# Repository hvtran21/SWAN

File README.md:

# Secure Wireless Authentication Network (SWAN) Electrical & Computer Engineering Class of 2025

## Overview
**SWAN (Secure Wireless Authentication Network)** is a senior capstone project focused on developing a safer, more seamless alternative to traditional RFID and NFC-based access systems.  

Current wireless access solutions, such as student ID cards or key fobs, suffer from two major issues:
1. **Security vulnerabilities** – Devices such as the Flipper Zero can easily clone, replay, or brute-force RFID/NFC signals, compromising access control systems.  
2. **Limited usability** – Cards must be presented within a few centimeters of a scanner, which is inconvenient when carrying items (e.g., food, books, bags) and detracts from user experience.

SWAN leverages **Ultra-Wideband (UWB) technology** to deliver both stronger security and automatic, hands-free authentication.  

---

## Problem Statement
Existing RFID and NFC access systems are vulnerable and inconvenient:
- **Vulnerabilities**: RFID/NFC cards transmit predictable signals that can be intercepted and cloned.  
- **User experience**: Scanning requires close proximity, forcing users to stop what they’re doing to present their ID.  

This is especially problematic in settings like dormitories or offices where secure yet convenient access is critical.

---

## Solution
SWAN provides an **automatic, secure, and user-friendly wireless authentication system** powered by **UWB**.  

Key design features:
- **Hardware**:  
  - Custom-designed PCBs  
  - **ESP32-C3 WROOM** microcontroller  
  - **Decawave DWM3000 UWB transceiver**  
- **Architecture**:  
  - A distributed network of devices with a **home anchor** that verifies access  
  - Automatic authentication within a defined UWB range (no card-swipe required)  
- **Security**:  
  - Communication encrypted using **AES-128**, the standard for low-power embedded devices  
  - Resistant to replay and cloning attacks compared to RFID/NFC
  - Back method to lost tags which includes an optical finger print reader, independent from the anchor removing depedency.
 
### What this enables
The idea is that these `tag` devices can take space in your wallet as a card, and something on your keychain.
These are items that you typically always have on your person, and want to keep import track of. In the unfortunate event 
that one of these devices are stolen, rest assured you're provided with a back biometric feature and that **two** tags 
must be present at all times.

---

## Benefits
- **Improved security**: Protects against Flipper Zero-style exploits and unauthorized duplication.  
- **Hands-free access**: Users can enter secured areas automatically, without swiping or tapping a card.  
- **Energy-efficient**: Designed with low-power embedded constraints in mind.  
- **Scalable**: Can be deployed in dorms, offices, or any facility requiring secure access.  

---

## Technology Stack
- **Embedded Hardware**: ESP32-C3 WROOM, DWM3000 UWB  
- **Firmware**: C/C++ with ESP-IDF and Arduino frameworks  
- **Networking**: UWB communication protocol, AES-128 encryption  
- **Custom PCBs**: Designed for modularity and integration with door access hardware

---

# Pictures

## Tag PCB v3

## Home Anchor PCB v1

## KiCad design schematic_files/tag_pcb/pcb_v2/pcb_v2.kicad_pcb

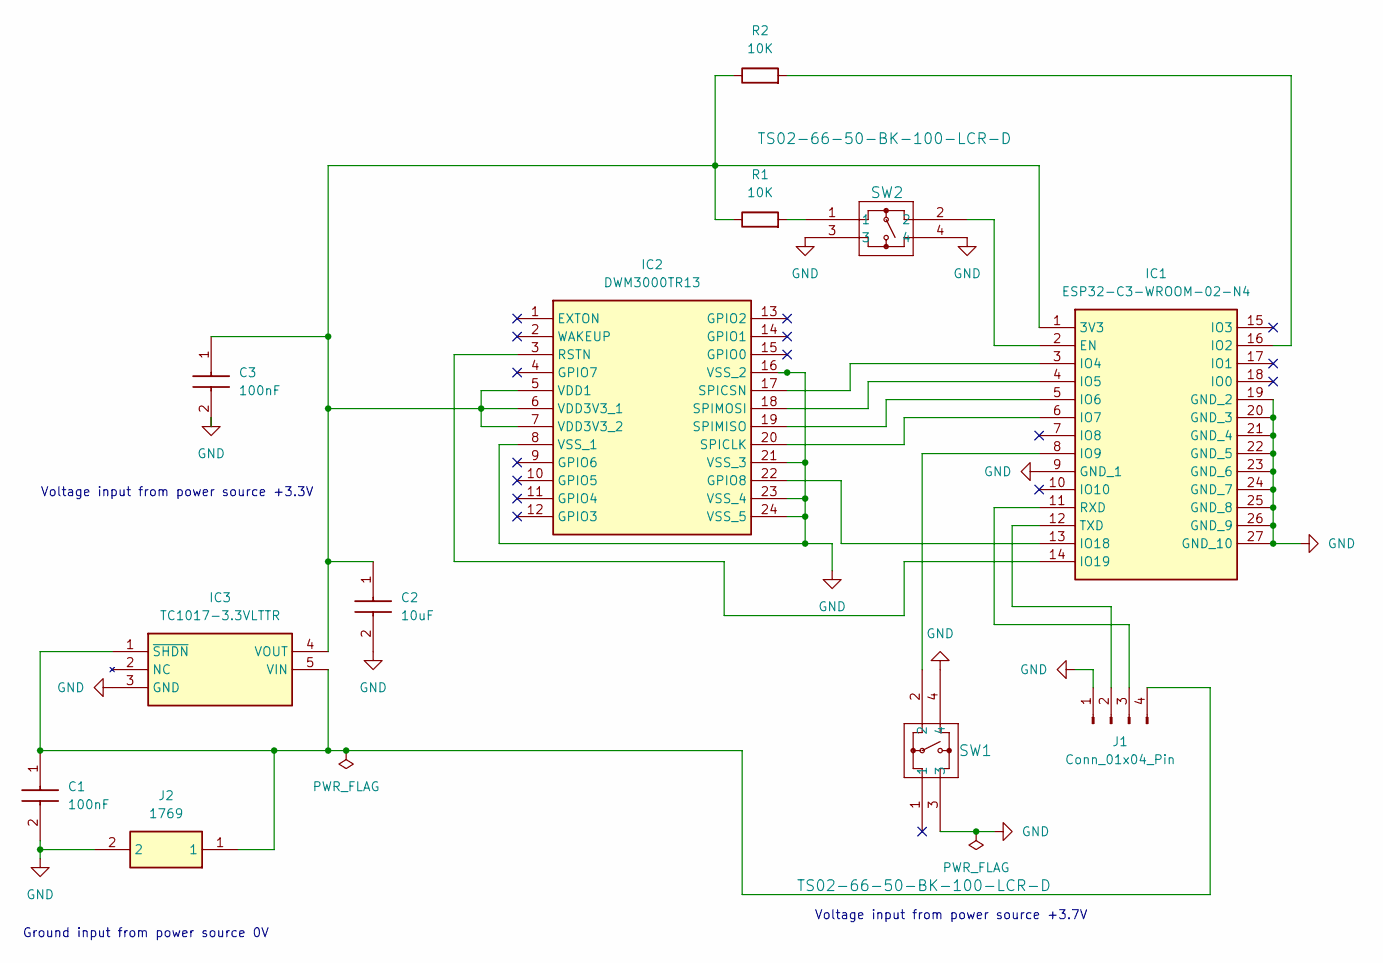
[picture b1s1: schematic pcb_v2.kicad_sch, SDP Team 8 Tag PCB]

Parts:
C1, C3: 100nF; CAPC2012X94N; Mouser Part Number 581-KAM21BR71H104JT
C2: 10uF; CAPC2012X140N; Mouser Part Number 81-GCM21BD70J106KE2L
IC1: ESP32-C3-WROOM-02-N4; ESP32C3WROOM02N4; Mouser Part Number 356-ESP32C3WROOM02N4
IC2: DWM3000TR13; XCVR_DWM3000TR13; Mouser Part Number 772-DWM3000TR13
IC3: TC1017-3.3VLTTR; SOT65P210X110-5N; Mouser Part Number 579-TC1017-3.3VLTTR
J1: Conn_01x04_Pin; PinHeader_1x04_P2.54mm_Vertical
J2: 1769; Mouser Part Number 485-1769
R1, R2: 10K; RESC3216X65N
SW1, SW2: TS02-66-50-BK-100-LCR-D; 6mm_push_button_footprint

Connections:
GND: C1.2, C2.2, C3.2, IC1.9 (GND_1), IC1.19 (GND_2), IC1.20 (GND_3), IC1.21 (GND_4), IC1.22 (GND_5), IC1.23 (GND_6), IC1.24 (GND_7), IC1.25 (GND_8), IC1.26 (GND_9), IC1.27 (GND_10), IC2.8 (VSS_1), IC2.16 (VSS_2), IC2.21 (VSS_3), IC2.23 (VSS_4), IC2.24 (VSS_5), IC3.3 (GND), J1.1, J2.2, SW1.3, SW1.4, SW2.3, SW2.4
unnamed: C2.1, C3.1, IC1.1 (3V3), IC2.5 (VDD1), IC2.6 (VDD3V3_1), IC2.7 (VDD3V3_2), IC3.4 (VOUT), R1.1, R2.1
unnamed: IC1.2 (EN), SW2.2
unnamed: IC1.16 (IO2), R2.2
unnamed: IC1.3 (IO4), IC2.17 (SPICSN)
unnamed: IC1.4 (IO5), IC2.18 (SPIMOSI)
unnamed: IC1.5 (IO6), IC2.19 (SPIMISO)
unnamed: IC1.6 (IO7), IC2.20 (SPICLK)
unnamed: IC1.8 (IO9), SW1.2
unnamed: IC1.13 (IO18), IC2.22 (GPIO8)
unnamed: IC1.14 (IO19), IC2.3 (RSTN)
unnamed: IC1.11 (RXD), J1.3
unnamed: IC1.12 (TXD), J1.2
unnamed: C1.1, IC3.1 (~SHDN), IC3.5 (VIN), J1.4, J2.1
unnamed: R1.2, SW2.1

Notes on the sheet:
Ground input from power source 0V
Voltage input from power source +3.7V
Voltage input from power source +3.3V

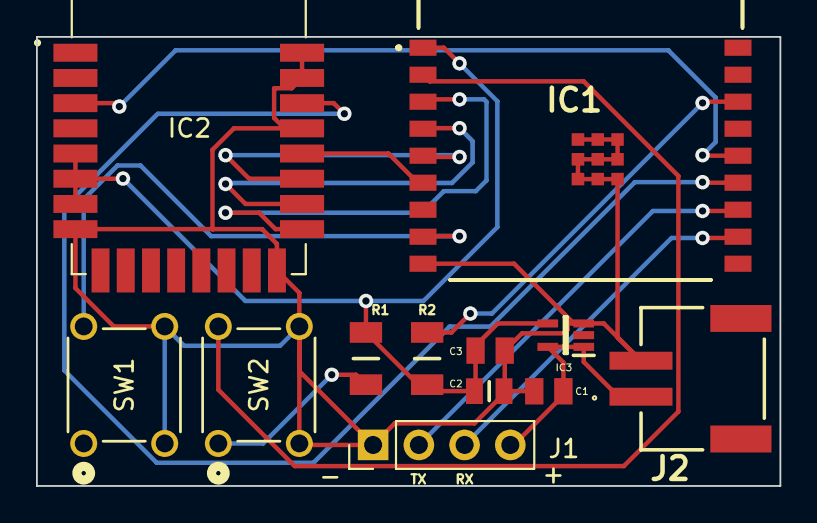
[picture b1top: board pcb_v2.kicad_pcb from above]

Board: 2 copper layers, 41.3 x 24.9 mm, 12 parts (0 on the bottom side), 15 nets.

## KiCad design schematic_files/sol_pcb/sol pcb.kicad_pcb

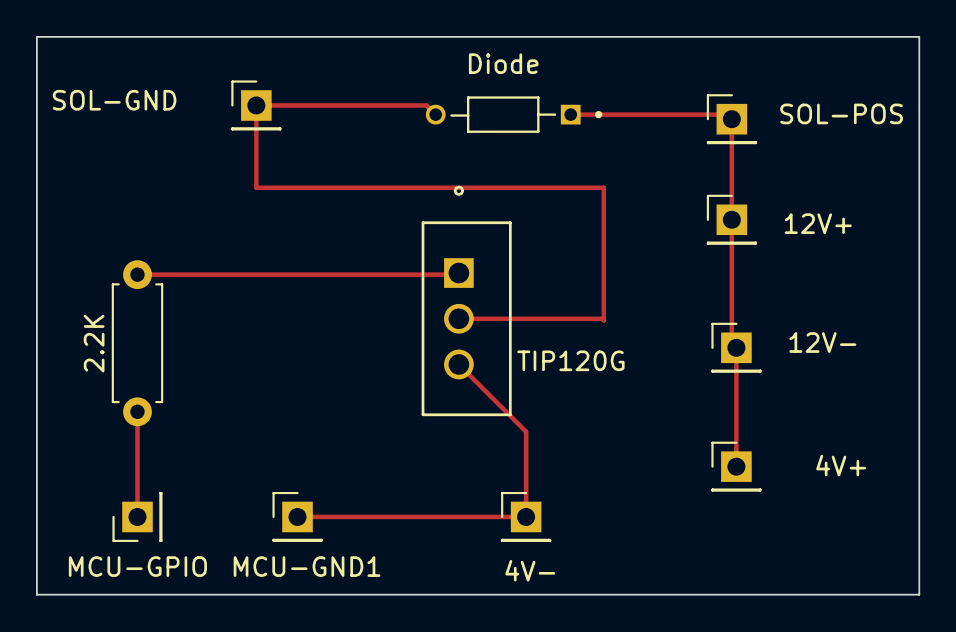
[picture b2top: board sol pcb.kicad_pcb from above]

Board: 2 copper layers, 49.0 x 31.0 mm, 11 parts (0 on the bottom side), 5 nets.

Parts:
2.2K: R; R_Axial_DIN0207_L6.3mm_D2.5mm_P7.62mm_Horizontal
4V+, 4V-, 12V+, 12V-: Conn_01x01_Pin; PinHeader_1x01_P2.54mm_Vertical
Diode: 1N4150; DIOAD750W50L390D190
MCU-GND1: Conn_01x01_Pin; PinHeader_1x01_P2.54mm_Vertical
MCU-GPIO: Conn_01x01_Pin; PinHeader_1x01_P2.54mm_Vertical
SOL-GND: Conn_01x01_Pin; PinHeader_1x01_P2.54mm_Vertical
SOL-POS: Conn_01x01_Pin; PinHeader_1x01_P2.54mm_Vertical
TIP120G: TIP120G; TO-220_STM

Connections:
GND: 4V-.1, MCU-GND1.1, TIP120G.3 (E)
unnamed: 4V+.1, 12V+.1, 12V-.1, Diode.1, SOL-POS.1
unnamed: 2.2K.1, MCU-GPIO.1
unnamed: 2.2K.2, TIP120G.1 (B)
unnamed: Diode.2, SOL-GND.1, TIP120G.2 (C)

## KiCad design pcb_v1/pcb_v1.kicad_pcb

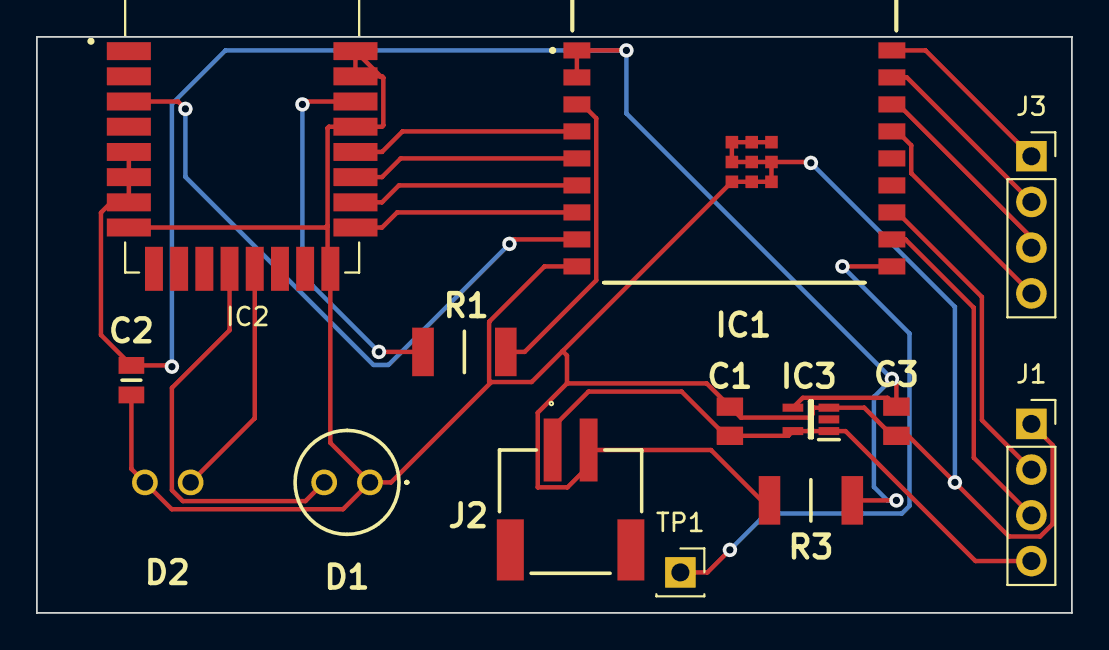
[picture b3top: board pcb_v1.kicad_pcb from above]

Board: 2 copper layers, 57.5 x 32.0 mm, 14 parts (1 on the bottom side), 19 nets.

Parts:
C1, C3: 100nF; CAPC2012X94N
C2: 10uF; CAPC2012X140N
D1, D2: LED; QED123A4R0
IC1: ESP32-C3-WROOM-02-N4; ESP32C3WROOM02N4
IC2: DWM3000TR13; XCVR_DWM3000TR13
IC3: TC1017-3.3VLTTR; SOT65P210X110-5N
J1, J3: Conn_01x04_Pin; PinSocket_1x04_P2.54mm_Vertical
J2: 1769
R1, R3: 100k Ohm; RESC5025X65N
TP1: Boot; PinSocket_1x01_P2.54mm_Vertical

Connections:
GND: C1.2, C2.2, C3.2, D1.1 (K), D2.1 (K), IC1.9 (GND_1), IC1.19 (GND_2), IC1.20 (GND_3), IC1.21 (GND_4), IC1.22 (GND_5), IC1.23 (GND_6), IC1.24 (GND_7), IC1.25 (GND_8), IC1.26 (GND_9), IC1.27 (GND_10), IC2.8 (VSS_1), IC2.16 (VSS_2), IC2.21 (VSS_3), IC2.23 (VSS_4), IC2.24 (VSS_5), IC3.3 (GND), J1.1, J2.2, R3.2
unnamed: D1.2 (A), IC2.12 (GPIO3)
unnamed: D2.2 (A), IC2.13 (GPIO2)
unnamed: IC1.18 (IO0), J3.1
unnamed: IC1.17 (IO1), J3.2
unnamed: IC1.16 (IO2), J3.3
unnamed: IC1.15 (IO3), J3.4
unnamed: IC1.3 (IO4), R1.2
unnamed: IC1.4 (IO5), IC2.20 (SPICLK)
unnamed: IC1.5 (IO6), IC2.19 (SPIMISO)
unnamed: IC1.6 (IO7), IC2.18 (SPIMOSI)
unnamed: IC1.7 (IO8), IC2.17 (SPICSN)
unnamed: IC1.8 (IO9), IC2.3 (RSTN)
unnamed: IC1.10 (IO10), TP1.1
unnamed: IC1.11 (RXD), J1.3
unnamed: IC1.12 (TXD), J1.2
unnamed: IC2.22 (GPIO8), R1.1
unnamed: C1.1, IC3.1 (~SHDN), IC3.5 (VIN), J1.4, J2.1
VDD: C2.1, C3.1, IC1.1 (3V3), IC1.2 (EN), IC2.5 (VDD1), IC2.6 (VDD3V3_1), IC2.7 (VDD3V3_2), IC3.4 (VOUT), R3.1

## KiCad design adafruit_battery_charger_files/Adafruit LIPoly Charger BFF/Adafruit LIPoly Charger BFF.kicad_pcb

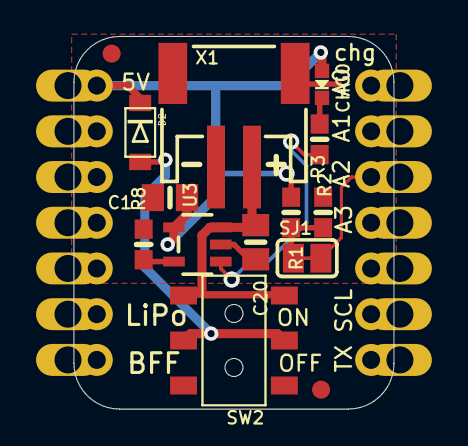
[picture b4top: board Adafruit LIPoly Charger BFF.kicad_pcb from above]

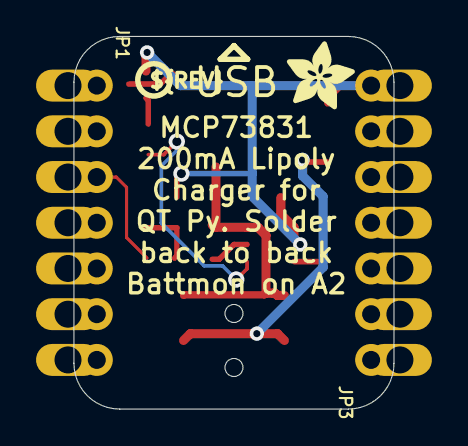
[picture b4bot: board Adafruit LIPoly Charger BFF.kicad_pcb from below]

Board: 16 copper layers, 17.8 x 20.7 mm, 18 parts (4 on the bottom side), 9 nets.

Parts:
C1, C20: 10µF; 0805-NO
CHG0: ORANGE; CHIPLED_0603_NOOUTLINE
D2: MBR120; SOD-123FL
JP1, JP3: 1X07_CASTEL
R1, R3: 100K; 0603-NO
R2, R8: 5.1K; 0603-NO
SJ1: SOLDERJUMPER_CLOSEDWIRE
SW2: EG1390
U3: MCP73831T-2ACI/OT; SOT23-5
U$2: ADAFRUIT_3.5MM
U$3: PCBFEAT-REV-040
U$6, U$8: FIDUCIAL_1MM
X1: JSTPH; JSTPH2_BATT

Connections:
+5V: C1.1, CHG0.A, D2.C, JP3.7, JP3.7C, R1.1, U3.4
A2: JP1.3, JP1.3C, SJ1.2
GND: C1.2, C20.2, JP3.6, JP3.6C, R3.2, R8.2, U3.2, X1.1, X1.NC1, X1.NC2
unnamed: R1.2, R3.1, SJ1.1
unnamed: CHG0.C, R2.1
unnamed: R2.2, U3.1
unnamed: R8.1, U3.5
unnamed: D2.A, SW2.P1, SW2.P2
VBAT: C20.1, SW2.S1, SW2.S2, U3.3, X1.2

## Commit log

2024-10-17 initial commit; add pcb, schem and datasheets
2024-10-20 add uwb kicad project files
2024-10-20 change name of uwb proj folder
2024-10-20 clean kicad file dir
2024-10-20 add uwb dwm3000 footprint files, located in dwm3000_footprint directory. add kicad project files, contains uwb schematic.
2024-10-24 add different schematic/pcb files for updated esp32 mcu
2024-10-24 move esp32 files to footprint dir for kicad use
2024-10-24 add new voltage regulator, since we need an LDO to regulate 3.7v to 3.3v
2024-10-24 first revision of swan pcb. note that this includes a horizontal 2x3 pinout for flashing code to the mcu. decided to move the powersource from battery completely off PCB, and perhaps is a seperate co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
2024-10-24 new kicad file was created in order to attempt to copy schematic files and symbols into a global library. moving away from these devices, ignore these files
2024-10-24 uwb pcb autosave backups, not important.
2024-10-29 add schem files for capacitors and resistors, will be using smd componenets. added footprint assignments to pcb, so there will be changes there, but those footprint assignments are local. you must go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
2024-10-29 move .*mod files to footprint directories for new schematic files
2024-10-29 update pcb with current schematic, assigned footprints to caps and res, didn't wire anything
2024-10-31 pcb edits. add led footprints
2024-10-31 update pin for jake baby
2024-11-06 Update README.md
    add link for esp-32 development
2024-11-06 files for esp32 development. added li poly charger connector to schematic build.
2024-11-07 added a test hello_world project, which would connect and communicate to the esp32c3-wroom-02 chip (dev-board). there are pre-reqs in order to run this project, you need to install esp-idf VSC extens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
2024-11-07 move component files to a different directory to clean up the root directory
2024-11-07 change mcu to esp32-c3-wroom, matches mcu on devboard kit.
2024-11-07 update pcb to use new mcu. the antennas are hanging off the pcb, and there are additional 1x4 pin headers for interfacing with unused GPIO pins just incase, and to flash code rx/tx.
2024-11-12 small changes to pcb, removed resistors and edited spi pins that connect mcu to uwb
2024-11-21 fix wiring issue, EN pin on esp32 always grounded
2024-11-21 add software files used to prorgram the UWB chips
2024-11-24 edit SPI configuration to work with custom PCB, and added config for GPIO port to switch to HIGH when tag is <= 1meter (rx)
2024-12-03 got working anchor code
2024-12-04 two tags working, checks distance from both tags sending two seperate requests and calculating time of flight
2024-12-04 fix paste issue in tx
2025-01-30 add .gitignore file
2025-01-30 clean up repo. all kicad schematic files should be stored in schematic_files, and only include just the .kicad_sch and .kicad_pcb
2025-02-03 add esp32 c3 datasheet
2025-02-03 add txt for pin assignment changes
2025-02-03 add push button schem and footprint
2025-02-03 rename folders for consistency
2025-02-04 add 10k footprint and symbol. Not using the symbol, just the footprint, but though to add it just in case.
2025-02-04 add kicad files. added pcb_v1 just for consistency. you must have the library files loaded in order for the project file to be opened with success
2025-02-04 add changelog.txt. This consists of changes to the PCB project. Stay updated on this since it will alleviate headaches later on
2025-02-12 update range_rx arduino to most recent revision
2025-02-21 add solenoid pcb
2025-02-21 Move component files to correct directory
2025-02-21 Add files via Upload :)
2025-02-21 Remove space in directory containing solenoid pcb. Added back silkscreen containing our group number
2025-02-21 Add .gbr and .drl files for JLCPCB
2025-03-04 gbr .zip files added for pcb order
2025-03-04 add notes for power analysis
2025-03-04 add power analysis for tag
2025-03-05 add pin definitions txt due to varying SPI pin setups across different PCB versions
2025-03-27 backups addd
2025-03-27 add fingerprint.ino file; working now
2025-03-27 add pcb_v2 files
2025-04-09 fix delay between when tags enter range to when anchor can recognize that. update file names to make it obvious what is what.
2025-04-11 update esp32 documentation file name
2025-04-11 add tag pcb kicad files. added tag .gbr files required for jlcpcb fab
2025-04-22 Webserver ino files
    change const char *ssid and const char *password to switch wifi networks. Connect anchor TX to GPIO 4
2025-08-21 Fix grammar issue and add detail
